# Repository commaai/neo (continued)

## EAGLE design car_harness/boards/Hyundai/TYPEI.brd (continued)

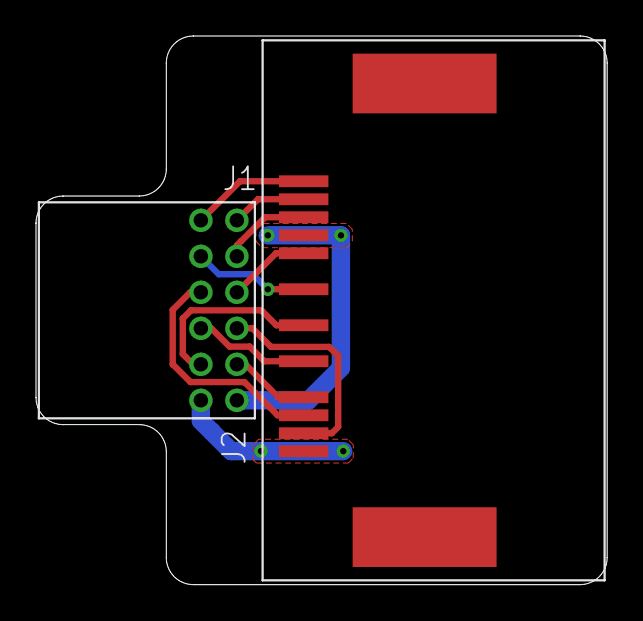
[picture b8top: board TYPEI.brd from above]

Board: 2 copper layers, 31.7 x 30.5 mm, 4 parts (1 on the bottom side), 12 nets.

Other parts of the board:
U$1: LOGO
